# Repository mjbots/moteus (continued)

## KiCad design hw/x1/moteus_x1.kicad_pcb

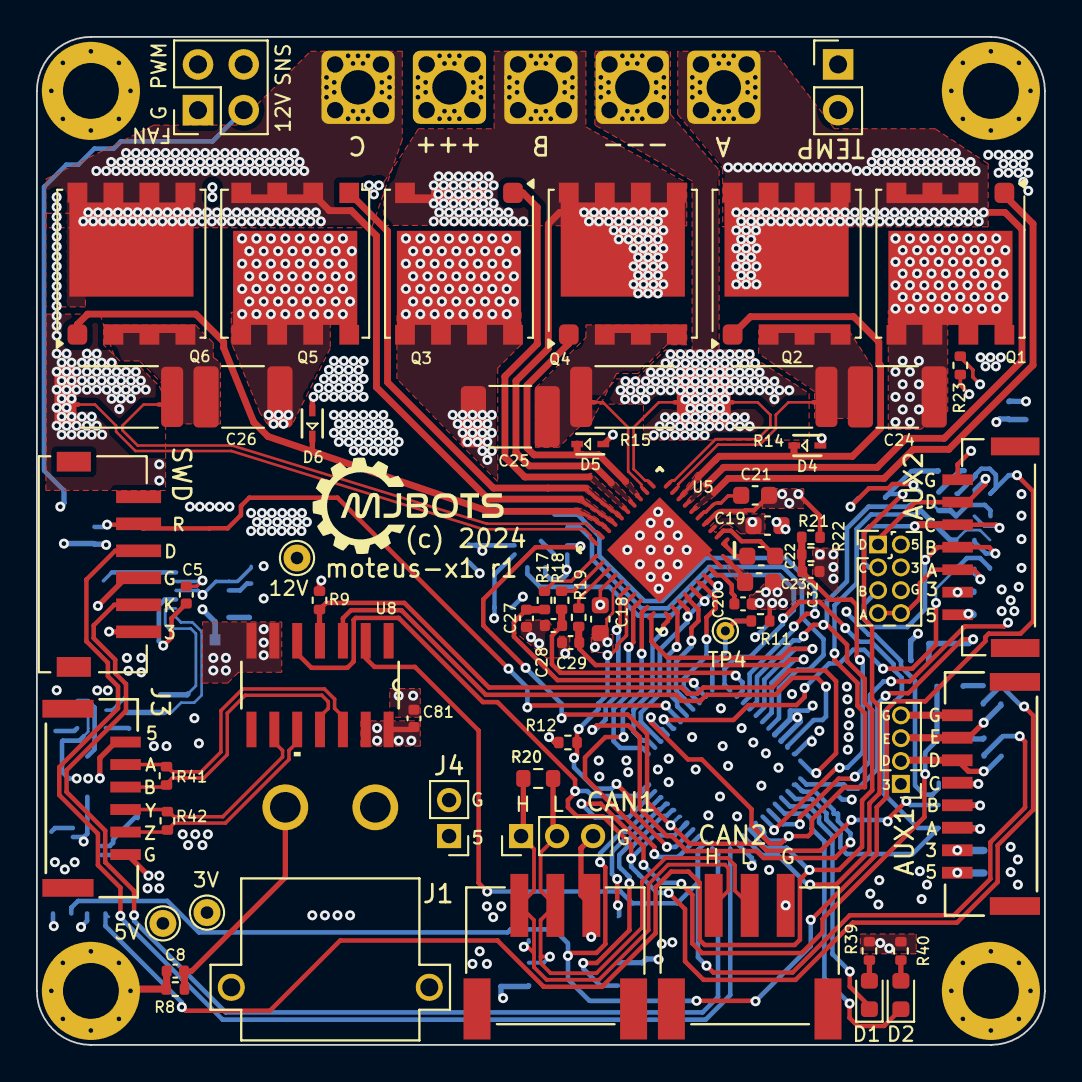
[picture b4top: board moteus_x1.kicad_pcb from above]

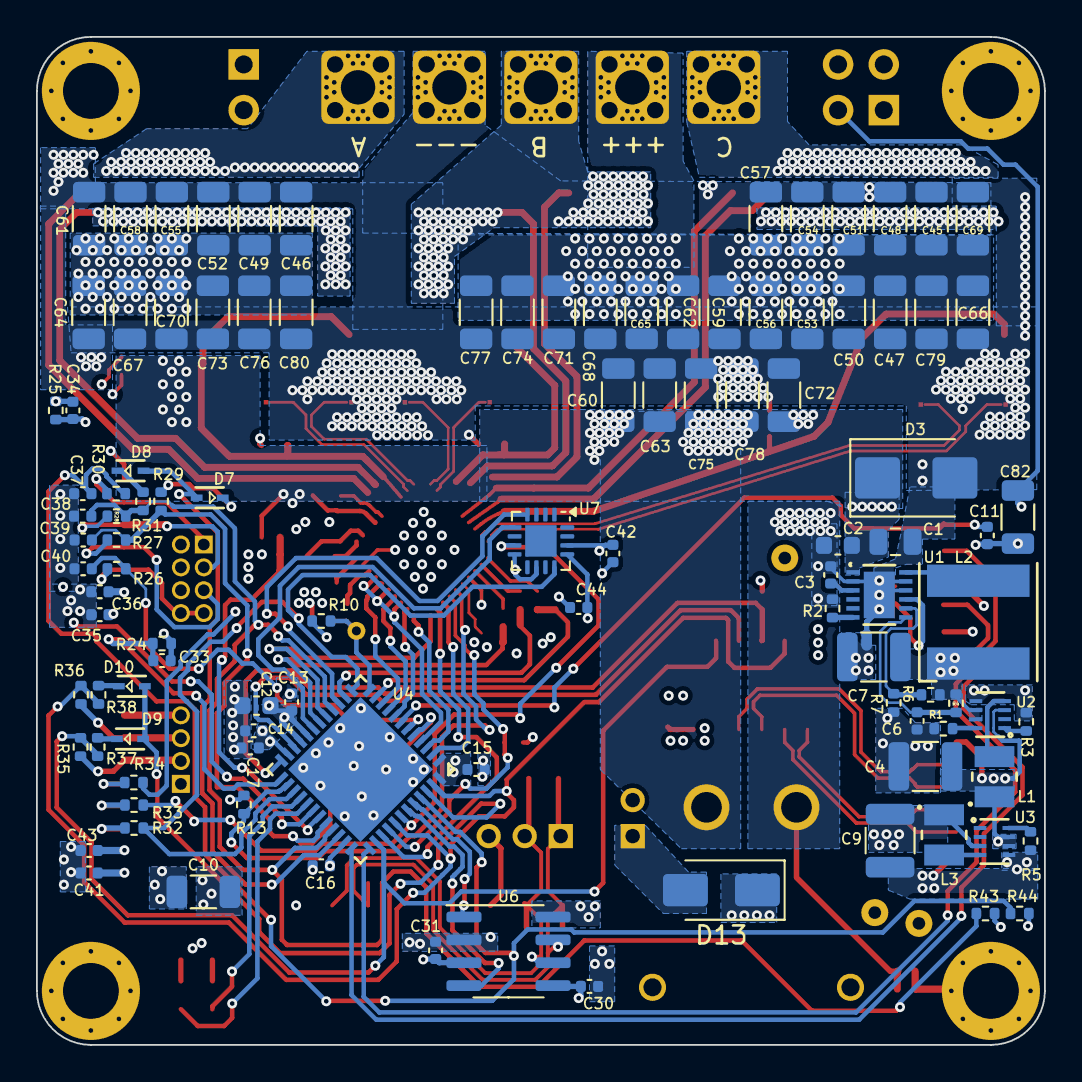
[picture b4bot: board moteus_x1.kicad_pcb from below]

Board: 6 copper layers, 56.0 x 56.0 mm, 187 parts (108 on the bottom side), 106 nets.

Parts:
AUX1: SM08B-GHS-TB; CONN_SM08B-GHS-TB_JST
AUX1_S1: Conn_01x04; PinHeader_1x04_P1.27mm_Vertical
AUX2: SM07B-GHS-TB(LF)(SN); JST_SM07B-GHS-TB(LF)(SN)
AUX2H1: Conn_02x04_Odd_Even; PinHeader_2x04_P1.27mm_Vertical
C1: 1uF 100V; C_0805_2012Metric
C2, C19: 0.1uF 100V; C_0603_1608Metric
C3, C6, C14, C20, C35, C36, C41, C42, C43: 1uF; C_0402_1005Metric
C4, C7, C9: 22uF; C_1210_3225Metric
C5: 5600pF; C_0402_1005Metric
C8, C37, C38, C39, C40: DNP; C_0402_1005Metric
C10: 10uF; C_1206_3216Metric
C11, C13, C15, C16, C17, C30, C31, C32, C33, C34, C44, C81: 0.1uF; C_0402_1005Metric
C12: 4.7uF; C_0603_1608Metric
C18, C23: 1uF; C_0603_1608Metric
C21: 1uF 25V; C_0603_1608Metric
C22: 47nF 100V; C_0603_1608Metric
C24, C25, C26: 0.1uF 100V; C_1812_4532Metric
C27, C28, C29: 1000pF; C_0402_1005Metric
C45, C46, C47, C48, C49, C50, C51, C52, C53, C54, C55, C56, C57, C58, C59, C60, C61, C62, C63, C64, C65, C66, C67, C68, C69, C70, C71, C72, C73, C74, C75, C76, C77, C78, C79, C80: 4.7uF 100V; C_1206_3216Metric
C82: 4.7uF; C_1206_3216Metric
CAN1, CAN2: S3B-PH-SM4-TB(LF)(SN); JST_S3B-PH-SM4-TB(LF)(SN)
CAN_DBG1: Conn_01x03_Pin; PinHeader_1x03_P2.00mm_Vertical
D1, D2: LED; LED_0603_1608Metric
D3: SMBJ51D-M3/I; D_SMB
D4, D5, D6, D7, D8, D9, D10: BAT41KFILM; SOD-523_STM
D13: US1B; D_SMA
FAN1: Conn_01x04_Pin; PinSocket_2x02_P2.54mm_Vertical
J1: XT30PW-M; AMASS_XT30PW-M
J3: SM06B-GHS-TB; CONN_SM06B-GHS-TB_JST
J4: Conn_01x02_Pin; PinHeader_1x02_P2.00mm_Vertical
L1, L3: 2.2uH; IND_DFE252012_MUR
L2: 100uH; IND_6028-WE-LQS_WRE
M1, M2, M3, M4: Conn_01x01_Pin; M3_MOUNT_CORNER
NT1: NetTie_2; NetTie-2_SMD_Pad0.254mm
NT2, NT3, NT4, NT5, NT6, NT7: NetTie_2; NetTie-2_SMD_Pad0.2
Q1, Q2, Q3, Q4, Q5, Q6: FDMT80080DC; PQFN_8x8
R1: 42.2k 1%; R_0402_1005Metric
R2: 69.8k 1%; R_0402_1005Metric
R3: 80.6k 1%; R_0402_1005Metric
R4, R17, R18, R19: 22; R_0402_1005Metric
R5: 52.3k 1%; R_0402_1005Metric
R6: 226k 1%; R_0402_1005Metric
R7: 16.2k 1%; R_0402_1005Metric
R8, R10: DNP; R_0402_1005Metric
R9, R12, R13, R29, R31, R37, R38: 2k; R_0402_1005Metric
R11, R21: 100k 1%; R_0402_1005Metric
R14, R15, R16: 0.5mOhm; R_2512_6332Metric
R20: 120; R_0603_1608Metric
R22: 4.7k 1%; R_0402_1005Metric
R23: 47k NTC; R_0402_1005Metric
R24, R25: 10k 1%; R_0402_1005Metric
R26, R27, R28, R30, R32, R33, R34, R35, R36, R43, R44: 100; R_0402_1005Metric
R39, R40: 560; R_0402_1005Metric
R41, R42: 120; R_0402_1005Metric
SWD1: S6B-ZR-SM4A-TF(LF)(SN); JST_S6B-ZR-SM4A-TF(LF)(SN)
TEMP1: Conn_01x02_Pin; PinHeader_1x02_P2.54mm_Vertical
TP1, TP2, TP3: TestPoint; TestPoint_THTPad_D1.5mm_Drill0.7mm
TP4: TestPoint; TestPoint_THTPad_D1.0mm_Drill0.5mm
U1: MAX17760ATC+; 21-0664E_1233-1C_MXM
U2, U3: TPS629203DRLR; SOT-5x3_DRL0008A_TEX
U4: STM32G474CEU6; UFQFPN-48_7X7X0P55MM
U5: DRV8353SRTAR; RTA0040B
U6: TCAN1057AEV-Q1; SOIC-8_3.9x4.9mm_P1.27mm
U7: MA600; QFN-16-1EP_3x3mm_P0.5mm_EP1.75x1.75mm
U8: SN65HVD35DR; D14
VN1: Conn_01x01; POWER_M2.5
VP1: Conn_01x01; POWER_M2.5
X1, X2, X3: Conn_01x01; POWER_M2.5

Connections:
+3V: AUX1.2, AUX1_S1.1, AUX2.2, AUX2H1.4, C9.1, C10.1, C12.1, C13.1, C14.1, C15.1, C16.1, C17.1, C18.2, C30.1, C36.1, C42.1, C43.1, C44.1, C81.1, L3.1, R10.1, R12.1, R13.1, R23.1, R39.1, R40.1, SWD1.6, TEMP1.1, TP3.1, U3.3 (VOS), U4.1 (VBAT), U4.20 (VREF+), U4.21 (VDDA), U4.23 (VDD), U4.35 (VDD), U4.48 (VDD), U5.24 (VREF), U6.5 (VIO), U7.13 (VDD), U7.14 (AVDD), U8.13 (VCC), U8.14 (VCC)
+5V: AUX1.1, AUX2.1, AUX2H1.2, C4.1, C31.1, C35.1, C41.1, D13.1 (K), J3.1, L1.1, TP1.1, U2.3 (VOS), U3.6 (VIN), U3.7 (EN), U6.3 (VCC)
+12V: C7.1, C19.2, C82.1, FAN1.2, L2.1, R4.2, R6.1, TP2.1, U2.6 (VIN), U2.7 (EN), U5.3 (VM)
/CAN/CAN_N: CAN1.2, CAN2.2, CAN_DBG1.2, R20.2, U6.6 (CANL)
/CAN/CAN_P: CAN1.1, CAN2.1, CAN_DBG1.1, R20.1, U6.7 (CANH)
/CAN/CAN_RX: U4.43 (PB5), U6.4 (RXD)
/CAN/CAN_TX: U4.44 (PB6), U6.1 (TXD)
/Current Sense/CUR1: R17.1, U5.21 (SOC)
/Current Sense/CUR2: R18.1, U5.22 (SOB)
/Current Sense/CUR3: R19.1, U5.23 (SOA)
/Current Sense/FCUR1: C27.1, R17.2, U4.11 (PA3)
/Current Sense/FCUR2: C28.1, R18.2, U4.14 (PA6)
/Current Sense/FCUR3: C29.1, R19.2, U4.18 (PB1)
/Gate Driver/CPH: C22.2, U5.2 (CPH)
/Gate Driver/CPL: C22.1, U5.1 (CPL)
/Gate Driver/DRV8323_CS: U4.17 (PB0), U5.30 (SCS_N)
/Gate Driver/DRV8323_FAULT: R13.2, U4.26 (PB13), U5.26 (FAULT_N)
/Gate Driver/DRV8323_MISO: R12.2, U4.40 (PC11), U5.27 (SDO)
/Gate Driver/DRV8323_MOSI: U4.2 (PC13), U5.28 (SDI)
/Gate Driver/DRV8323_SCLK: U4.39 (PC10), U5.29 (SCLK)
/Gate Driver/GHA: Q1.1 (G), U5.6 (GHA)
/Gate Driver/GHB: Q3.1 (G), U5.15 (GHB)
/Gate Driver/GHC: Q5.1 (G), U5.16 (GHC)
/Gate Driver/GLA: D4.1, Q2.1 (G), U5.8 (GLA)
/Gate Driver/GLB: D5.1, Q4.1 (G), U5.13 (GLB)
/Gate Driver/GLC: D6.1, Q6.1 (G), U5.18 (GLC)
/Gate Driver/MOTOR1: U4.8 (PA0), U5.32 (INHA)
/Gate Driver/MOTOR2: U4.9 (PA1), U5.34 (INHB)
/Gate Driver/MOTOR3: U4.10 (PA2), U5.36 (INHC)
/Gate Driver/MOTOR_ENABLE: U4.3 (PC14-OSC32_IN), U5.31 (ENABLE)
/Gate Driver/MOTOR_HIZ: U4.4 (PC15-OSC32_OUT), U5.33 (INLA), U5.35 (INLB), U5.37 (INLC)
/H Bridge A/OUTX: Q1.2 (S), Q2.3 (D), U5.7 (SHA), X1.1
/H Bridge A/SPX_Q: C24.2, NT2.2, Q2.2 (S), R14.1
/H Bridge A/SXX_N: NT3.1, U5.10 (SNA)
/H Bridge A/SXX_P: NT2.1, U5.9 (SPA)
/H Bridge B/OUTX: Q3.2 (S), Q4.3 (D), U5.14 (SHB), X2.1
/H Bridge B/SPX_Q: C25.2, NT4.2, Q4.2 (S), R15.1
/H Bridge B/SXX_N: NT5.1, U5.11 (SNB)
/H Bridge B/SXX_P: NT4.1, U5.12 (SPB)
/H Bridge C/OUTX: Q5.2 (S), Q6.3 (D), U5.17 (SHC), X3.1
/H Bridge C/SPX_Q: C26.2, NT6.2, Q6.2 (S), R16.1
/H Bridge C/SXX_N: NT7.1, U5.20 (SNC)
/H Bridge C/SXX_P: NT6.1, U5.19 (SPC)
/LED Sense/DAC: R10.2, R11.1, TP4.1, U4.12 (PA4)
/LED Sense/LED1: D1.1 (K), U4.28 (PB15)
/LED Sense/LED2: D2.1 (K), U4.29 (PC6)
/Power Input/5V_IN: D13.2 (A), J4.1
/VT Sense/VBAT_SENSE: C32.1, R21.2, R22.1, U4.31 (PA9)
/VT Sense/VTEMP_FET: C33.1, R23.2, R24.1, U4.25 (PB12)
/VT Sense/VTEMP_MOT: C34.1, R25.1, TEMP1.2, U4.30 (PA8)
/aux1/AS5047_CS: U4.19 (PB2), U7.5 (~CS)
/aux1/AUX1P_A: AUX1.3, R32.1
/aux1/AUX1P_B: AUX1.4, R33.1
/aux1/AUX1P_C: AUX1.5, R34.1
/aux1/AUX1P_D: AUX1.6, AUX1_S1.2, R35.1
/aux1/AUX1P_E: AUX1.7, AUX1_S1.3, R36.1
/aux1/AUX1_A: R32.2, U4.13 (PA5), U4.27 (PB14), U7.12 (SCLK)
/aux1/AUX1_B: R33.2, U4.42 (PB4), U7.7 (MISO)
/aux1/AUX1_C: R34.2, U4.15 (PA7), U7.4 (MOSI)
/aux1/AUX1_D: R35.2, R37.2, U4.38 (PA15), U8.2 (R)
/aux1/AUX1_E: R36.2, R38.2, U4.41 (PB3), U4.47 (PB9), U8.5 (D)
/aux1/AUX1_I2C_PULLUP: D9.2, D10.2, U4.46 (PB8-BOOT0)
/aux2/AUX2P_A: AUX2.3, AUX2H1.7, AUX2H1.8, R26.1
/aux2/AUX2P_B: AUX2.4, AUX2H1.5, R27.1
/aux2/AUX2P_C: AUX2.5, AUX2H1.3, R28.1
/aux2/AUX2P_D: AUX2.6, AUX2H1.1, R30.1
/aux2/AUX2_A: C40.1, R26.2, U4.6 (PF1-OSC_OUT)
/aux2/AUX2_B: C39.1, R27.2, R29.2, U4.5 (PF0-OSC_IN), U4.32 (PA10)
/aux2/AUX2_C: C38.1, R28.2, R31.2, R43.1, U4.16 (PC4), U4.33 (PA11)
/aux2/AUX2_D: C37.1, R30.2, R44.1, U4.45 (PB7)
/aux2/AUX2_I2C_PULLUP: D7.2, D8.2, U4.34 (PA12)
/rs422/RS422_DE: R9.1, U4.24 (PB11), U8.4 (DE)
/rs422/RS422_RE: U4.22 (PB10), U8.3 (*RE)
/rs422/RS422_RX_N: J3.3, R41.2, U8.11 (B)
/rs422/RS422_RX_P: J3.2, R41.1, U8.12 (A)
/rs422/RS422_TX_N: J3.5, R42.2, U8.10 (Z)
/rs422/RS422_TX_P: J3.4, R42.1, U8.9 (Y)
/stm32g4/NRST: C11.1, SWD1.2, U4.7 (PG10-NRST)
/stm32g4/SWCLK: SWD1.5, U4.37 (PA14)
/stm32g4/SWDIO: SWD1.3, U4.36 (PA13)
GND: AUX1.8, AUX1_S1.4, AUX2.7, AUX2H1.6, C4.2, C6.2, C7.2, C9.2, C10.2, C11.2, C12.2, C13.2, C14.2, C15.2, C16.2, C17.2, C18.1, C20.1, C23.1, C27.2, C28.2, C29.2, C30.2, C31.2, C32.2, C33.2, C34.2, C35.2, C36.2, C37.2, C38.2, C39.2, C40.2, C41.2, C42.2, C43.2, C44.2, C81.2, C82.2, CAN1.3, CAN2.3, CAN_DBG1.3, FAN1.1, J3.6, J4.2, NT1.2, R1.2, R3.2, R5.2, R7.2, R9.2, R11.2, R22.2, R24.2, R25.2, SWD1.4, U2.5 (GND), U3.5 (GND), U4.49 (EPAD), U5.25 (AGND), U6.2 (GND), U6.8 (STB), U7.8 (GND), U7.10 (TEST), U8.6 (GND), U8.7 (GND)
GNDPWR: C1.2, C2.2, C3.2, C5.2, C8.2, C19.1, C45.2, C46.2, C47.2, C48.2, C49.2, C50.2, C51.2, C52.2, C53.2, C54.2, C55.2, C56.2, C57.2, C58.2, C59.2, C60.2, C61.2, C62.2, C63.2, C64.2, C65.2, C66.2, C67.2, C68.2, C69.2, C70.2, C71.2, C72.2, C73.2, C74.2, C75.2, C76.2, C77.2, C78.2, C79.2, C80.2, D3.2 (A2), D4.2, D5.2, D6.2, J1.N, NT1.1, NT3.2, NT5.2, NT7.2, R2.2, R8.2, R14.2, R15.2, R16.2, U1.2 (PGND), U1.10 (MODE), U1.11 (SGND), U1.13 (EPAD), U5.39 (PGND), U5.41 (PAD), VN1.1
MOUNT_GND: C8.1, M4.1, R8.1
unnamed: D1.2 (A), R39.2
unnamed: D2.2 (A), R40.2
unnamed: D7.1, R29.1
unnamed: D8.1, R31.1
unnamed: D9.1, R37.1
unnamed: D10.1, R38.1
unnamed: FAN1.3, R44.2
unnamed: FAN1.4, R43.2
unnamed: C6.1, R4.1, U1.7 (EXTVCC)
unnamed: R6.2, R7.1, U1.8 (FB)
unnamed: L2.2, U1.12 (LX)
unnamed: R2.1, U1.6 (RT/SYNC)
unnamed: C5.1, U1.9 (SS)
unnamed: C3.1, U1.3 (VCC)
unnamed: R3.1, U2.1 (FB/VSET)
unnamed: R1.1, U2.8 (MODE/S-CONF)
unnamed: L1.2, U2.4 (SW)
unnamed: R5.1, U3.8 (MODE/S-CONF)
unnamed: L3.2, U3.4 (SW)
unnamed: C20.2, U5.38 (DVDD)
unnamed: C21.2, U5.5 (VCP)
unnamed: C23.2, U5.40 (VGLS)
V+: C1.1, C2.1, C21.1, C24.1, C25.1, C26.1, C45.1, C46.1, C47.1, C48.1, C49.1, C50.1, C51.1, C52.1, C53.1, C54.1, C55.1, C56.1, C57.1, C58.1, C59.1, C60.1, C61.1, C62.1, C63.1, C64.1, C65.1, C66.1, C67.1, C68.1, C69.1, C70.1, C71.1, C72.1, C73.1, C74.1, C75.1, C76.1, C77.1, C78.1, C79.1, C80.1, D3.1 (A1), J1.P, Q1.3 (D), Q3.3 (D), Q5.3 (D), R21.1, U1.1 (VIN), U5.4 (VDRAIN), VP1.1

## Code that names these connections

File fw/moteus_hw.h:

// Copyright 2023 mjbots Robotic Systems, LLC.  info@mjbots.com
//
// Licensed under the Apache License, Version 2.0 (the "License");
// you may not use this file except in compliance with the License.
// You may obtain a copy of the License at
//
//     http://www.apache.org/licenses/LICENSE-2.0
//
// Unless required by applicable law or agreed to in writing, software
// distributed under the License is distributed on an "AS IS" BASIS,
// WITHOUT WARRANTIES OR CONDITIONS OF ANY KIND, either express or implied.
// See the License for the specific language governing permissions and
// limitations under the License.

#pragma once

#include "mbed.h"

#include "fw/fet_thermal_model.h"
#include "fw/millisecond_timer.h"

namespace moteus {

//////////////////////////////////////////
// The following "families" are supported:
//  moteus-r4 - family 0
//  moteus-n1 - family 1
//  moteus-c1 - family 2
//  moteus-x1 - family 3
//  moteus-r5 - family 4
//
// Each family has an independent hardware version timeline, and
// possibly a different mechanism for verifying hardware version
// compatibility.


// This structure is filled in once the family and hardware version
// are known.
struct MoteusHwPins {
  PinName pwm1 = PA_0_ALT0;
  PinName pwm2 = PA_1_ALT0;
  PinName pwm3 = PA_2_ALT0;

  PinName drv8323_enable = NC;
  PinName drv8323_hiz = NC;
  PinName drv8323_cs = NC;

  PinName drv8323_mosi = NC;
  PinName drv8323_miso = NC;
  PinName drv8323_sck = NC;
  PinName drv8323_fault = NC;

  PinName debug_led1 = NC;
  PinName power_led = NC;

  PinName current1 = NC;
  PinName current2 = NC;
  PinName current3 = NC;

  PinName vsense = NC;
  PinName tsense = PA_9;

  PinName msense = NC;

  float vsense_adc_scale = 0.0f;

  PinName as5047_cs = NC;

  PinName can_td = NC;
  PinName can_rd = NC;

  PinName debug1 = NC;
  PinName debug2 = NC;
  PinName debug_dac = PA_4;

  uint32_t model_number = 0;

  uint32_t firmware_version = 0x000105;

  // Each board has a power limit curve, below a bus voltage V_l, the
  // P_l power limit is used.  Above bus voltage V_h, P_h power limit
  // is used.  Between, the power limit is linearly interpolated.  All
  // power limits are normalized to 30kHz PWM.
  float power_P_l_W = 0.0f;
  float power_V_l = 24.0f;
  float power_P_h_W = 0.0f;
  float power_V_h = 34.0f;

  // Constants for the FET junction temperature estimator.  Every
  // board must provide these.  See fw/fet_thermal_model.h.
  FetThermalParams fet_thermal;
};


struct FamilyAndVersion {
  int family = 0;
  int hw_version = 0;
  int hw_pins = 0;
};

// Return what family we are executing on.
FamilyAndVersion DetectMoteusFamily(MillisecondTimer*);

MoteusHwPins FindHardwarePins(FamilyAndVersion);


// The "FIRMWARE_VERSION" is a misnomer.  It instead is the equivalent
// of an ABI version, and is incremented when configuration values
// change in a way that would not result in equivalent behavior across
// an upgrade/downgrade.

// Version history:

// # 0x0101 #
//
// * Fixed the calculation of feedforward voltage to have the correct
//   sign for the velocity component.  Previous firmwares,
//   inappropriately applied a negative feedforward term, which
//   counteracted rotation instead of being an actual feedforward.

// # 0x0102 #
//
// * Removed servo.feedforward_scale entirely

// # 0x0103 #
//
// * Added servo.pwm_scale, and for r4.8 boards changed the default
//   value of pwm_comp_off / pwm_comp_mag.

// # 0x0104 #
//
// * Added configurable PWM rates, which changed default values of
//   pwm_comp_mag and pwm_comp_off.

// # 0x0105 #
//
// * Switched to a new encoder and position subsystem.

// # 0x0106 #
//
// * Switched aux?.sources.x.i2c.poll_ms to poll_rate_us to match UART
//   and give more resolution.

// # 0x0107 #
//
// * Fixed motor_position.output.sign == -1 so that DQ commands for
//   voltage or current are inverted, so that positive Q axis voltage
//   or current results in positive speed

// # 0x0108 #
//
// * The default value of `servo.bemf_feedforward` was changed from
//   1.0 to 0.0.

// # 0x0109 #
//
// * Commutation compensation now interpolates, which means old tables
//   need to be upgraded during the flash process.
// * The motor thermistor value is now configurable and defaults to
//   10k instead of 47k.

// # 0x010a #
//
// * servo.max_power_W now defaults to NaN, and if present is used as
//   an absolute value rather than as a "nominal" value.

// # 0x010b #
//
// * servo.flux_brake_margin_voltage replaces
//   servo.flux_brake_min_voltage
// * servo.temperature_margin replaces servo.derate_temperature
// * servo.motor_temperature_margin replaces
//   servo.motor_derate_temperature

// # 0x010c #
//
// * motor_position.sources.x.pll_filter_hz was previously specified
//   in terms of a somewhat arbitrary "natural frequency", but is now
//   specified in terms of the 3dB cutoff frequency

// # 0x010d #
//
// * aux?.rs422 replaced aux?.uart.rs422 as now the RS422 transceiver
//   can be enabled for both UART and BiSS-C encoders

// # 0x010e #
//
// * servo.pid_dq.kp/ki/max_desired_rate replaced by servo.pid_dq_hz
//   and servo.max_current_desired_rate.  PI gains are now computed
//   automatically from the bandwidth and motor parameters.

// # 0x010000
//
// No functional changes.  ABI release 1.0.0

// # 0x010100
//
// * The drv8323_conf reg4 calculation now maps idriven_ls_ma through the
//   DRV8353 pull-down (idriven) table instead of the pull-up (idrivep)
//   table.  DRV8353-board idriven_ls_ma defaults were adjusted and
//   moteus_tool migrates stored configs so the gate-drive register
//   output is unchanged across the upgrade.
// * The gate-driver family routing was corrected: moteus-c1 (family 2,
//   a DRV8323) now uses the drv8323 register path and moteus-n1
//   (family 1, a DRV8353) uses the drv8353 register path.  These were
//   swapped by an inadvertent "family == 1" clause in the c1-support
//   commit.  c1's defaults are adjusted (and configs migrated) to keep
//   its register output unchanged; n1's register output is restored to
//   what it was before the c1-support commit.
//
// ABI release 1.1.0

#define MOTEUS_MODEL_NUMBER 0x0000
#define MOTEUS_FIRMWARE_VERSION 0x010100

extern MoteusHwPins g_hw_pins;

// Ensure the DRV8323 is turned off.
void MoteusEnsureOff();

}

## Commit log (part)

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2026-05-15 Add jerk-limited online trajectory generation
    When data->jerk_limit is finite and positive, the position trajectory
    generator slews control_acceleration at no more than the configured
    rate per second, producing an S-curve velocity profile instead of a
    bang-bang trapezoidal one. The behavior reduces to the legacy path
    when jerk_limit is NaN, so out-of-the-box trajectories are unchanged.
    This is not a complete substitute for systems like ruckig, notably:
2026-05-15 Tighten bounds across jerk-related tests
    Replace generous safety factors with empirically-derived tight
    bounds. Tightening summary:
    - ResidualBound: 10x -> 1x safety factor over the analytical
    (kinematic_floor + drift_floor). Worst observed across all jerk
    tests is ~30% of the unscaled bound, so 1x retains >3x headroom.
    - JerkBoundFor + the duplicate in RunAndCheckJerkBound + the in-line
2026-05-15 Verify jerk-bound per cycle in JerkLimitedTakesLongerThanTrapezoidal
    The comment claimed the jerk-limited run should have no |Δa| > j*dt
    per cycle, but no such assertion existed. Add it: the run lambda
    now captures control_acceleration each cycle and (for the
    jerk-limited variant only) asserts |Δa| <= j*dt + accel*eps.
    Verified by replacing SlewAcceleration's per-cycle clamp with 2x the
    bound; the new check fires immediately (1.33 > 0.667).
2026-05-15 Test consolidation pass 2: subsume parameterizable singletons
    Three more groups subsumed into existing or new sweeps. Each
    consolidation was verified by reverting the relevant fix and
    confirming the consolidated test still catches the regression.
    Section E (mid-slew retargeting):
    - Extend JerkLimitRetargetAtEachPhase to accept `new_target`
    per row (was hard-coded 10.0) and to recognise `delay < 0`
2026-05-15 Stop NaN'ing data->position at jerk-limited termination
    The previous fix (c394983a) made the trajectory_done reset
    conditional on the commit latch -- but only protected the cycle
    the host frame actually arrived on. In production the host polls
    every ~2 ms, leaving ~60 ISR cycles between frames during which the
    FW used to NaN'd data->position out of the just-completed
    trajectory. The latch tolerance check (data->position == cp) then
2026-05-16 Add termination sweeps for four previously-uncovered scenarios
    Four new tests covering scenarios that production failures suggest
    the original tests do not exercise:
    - JerkLimitMoveLoopTermination: the moteus.move_to() loop pattern
    (a sequence of four same/different targets across two channels,
    three iterations). Catches any failure where consecutive moves
    to the same target oscillate or fail to terminate -- the exact
2026-05-16 Add hall lost-tracking recovery for stuck misaligned motors
    When hall sensors are physically misaligned (sector widths not
    uniformly 60° electrical), the firmware's filtered_value can coast
    forward to compensated + max_err during the wider sectors and then
    stay there once the motor stops -- with no transition to "reset"
    commutation, the firmware-reported electrical angle can sit nearly
    90° from the rotor's true angle, the projected q-axis torque
2026-05-19 Deployed 39e1a6a with MkDocs version: 1.6.1
2026-05-19 Do a better job estimating the ground truth hall position
    The find_ground_truth function used to return the start of a sector
    and velocity=0 when either the trace ended or when the rotor bounced
    back and forth.
    Instead, for end of trace return the center of the sector, and if the
    rotor bounced back and forth, return the boundary itself, as we have
    no real indication that it went into the sector at all.
2026-05-21 Deployed ad43136 with MkDocs version: 1.6.1
2026-05-21 Actually update CHANGELOG.md since the last release
2026-05-22 Deployed e1333e5 with MkDocs version: 1.6.1
2026-05-23 Fix more doc config typos
2026-05-23 Rewrite mypy_test to operate on the build files
    Previously it generated a fake version file in the actual source tree
    which was often left behind.
2026-05-24 Deployed eb7c5fc with MkDocs version: 1.6.1
2026-05-24 Deployed e4459e7 with MkDocs version: 1.6.1
2026-05-24 Release python 1.0.0rc2
2026-05-25 Release python 1.0.0rc3
2026-05-25 Release python 1.0.0rc4
2026-05-27 Fix multiple gate drive strength mapping issues and re-tune the n1
    There were two separate bugs in involved here.
    1. For drv8353 boards, we were accidentally using the gate mapping
    table for idrivep on the low side when we should have been using
    idriven.
    2. We were mis-characterizing moteus-c1 as a drv8353 board and have
    been mis-characterizing moteus-n1 as a drv8323 board since the
2026-05-28 Release python 1.0.0
2026-06-03 Fix the location of the default UART port
    The intention was that the default UART port would always be present
    on pins that were connectorized. That is what is documented.
    However, the actual implementation of this was broken, and moteus-c1
    got its default UART on aux1, whereas moteus-n1 got it on aux2. Swap
    those back to what was intended.
    Now, the default UARTs are at:
2026-06-03 Deployed ae2d7a77 with MkDocs version: 1.6.1
2026-06-03 Rust API: Fix MSRV to 1.75 (was incorrectly set to 1.85)
2026-06-03 Rust API: Fix version numbers in docs/integration/rust.md
2026-06-03 Rust API: Add Transport::from_device() for single-device construction
2026-06-03 Rust API: Use fixed-size arrays instead of Vec for single-request cycles
2026-06-03 Rust API: Add AsyncController
    - AsyncController: High-level async interface using tokio feature
    - Full module exports in lib.rs
2026-06-03 Rust API: Rename Request builder methods with with_ prefix
2026-06-03 Rust API: Add SocketCAN transport for Linux
    Add SocketCAN transport for native Linux CAN interfaces:
    - SocketCan: Linux kernel CAN interface support
    - CAN-FD frame send/receive
    - Interface enumeration
2026-06-03 Rust API: Fix all cargo clippy warnings
    Applied automatic fixes and manual corrections for: unnecessary casts
    left over from f64->f32 migration, doc comment overindentation,
    map_or -> is_none_or/is_some_and, derivable Default impl for
    FrameFilter, while_let_loop, iter().copied().collect() -> to_vec(),
    and suppressed needless_range_loop where refactoring would reduce
    readability.
2026-06-03 Rust API: Add #[non_exhaustive] to all public structs and enums
    Prevents future field or variant additions from being breaking changes
    for external crate users. Internal code is unaffected.
2026-06-03 Rust API: Fix moteus-protocol feature documentation
2026-06-03 Rust API: Revert edition to 2021 to preserve MSRV 1.75
2026-06-03 Rust API: Simplify Explicit Transport doc example
2026-06-03 Rust API: Fix SocketCanFactory references for cross-platform builds
    Cfg-gate get_factories(), get_async_factories(), and related tests
    that reference SocketCanFactory/AsyncSocketCanFactory so they only
    compile on Linux. This fixes builds on non-Linux platforms.
2026-06-03 Rust API: Add doc tests to bazel test suite, convert ignore to no_run
    Add rust_doc_test targets for both base and all-features variants.
    Convert all `ignore` doctests to `no_run` (compiled but not executed)
    where possible, and fix doc examples to compile correctly. Only 3
    examples remain `ignore` in the base target (require tokio/clap
    features) but are tested by the all-features variant.
2026-06-03 Rust API: Trim root re-exports to core types only
    Reduce the moteus crate root from ~46 re-exports to ~12 core types
    that most users need. Advanced types remain accessible through their
    public modules (e.g., moteus::diagnostic::DiagnosticStream,
    moteus::transport::transaction::Request). This makes auto-complete
    more useful and the API surface easier to understand.
2026-06-03 Rust API: Remove SocketCan stubs on non-Linux, cfg-gate factory impls
    SocketCan is only available on Linux. Rather than providing stub types
    that fail at runtime, cfg-gate the struct, factory impl, and registry
    entry so they simply don't exist on non-Linux platforms.
2026-06-03 Rust API: Add #[must_use] to derived setter methods
2026-06-03 Rust API: Make multiplex module pub(crate), keep scaling public
    The multiplex module's types are re-exported at the crate root; the
    raw protocol command byte constants are also re-exported for users who
    need them. The scaling module stays public since users interact with
    scaling consts directly via Value::to_f32().
2026-06-03 rust: Rename transport structures to match python more closely
    - the structures that directly communicate with a device now get a
    'Device' suffix like in python
    - the TransportOps trait is now Transport
    - the Transport struct is now Router
    Then, there are new wrappers named 'Fdcanusb' and 'SocketCan' which
    are a 'Router' that is composed of a single device of the given type.
2026-06-03 Rust API: Add transport registry for external factory registration
    External crates can now register transport factories via register() and
    register_async() so they participate in auto-detection. Adds extra field
    to TransportOptions for transport-specific key-value args, moves
    factory-specific arg specs into arg_specs() trait methods, and replaces
    static TRANSPORT_ARG_SPECS with dynamic transport_arg_specs().
2026-06-03 rust: Add separate READMEs for each crate
2026-06-03 Reset I2C peripherals that appear to be taking too long
    If the STM32 I2C peripheral attempts to start a transaction with when
    both lines read low, it will itself hold both lines low, wedging with
    no way to get unstuck. Thus we use a brute-force timeout to reset the
    peripheral if a response doesn't come in on time.
2026-06-03 Deployed 46ca6586 with MkDocs version: 1.6.1
2026-06-10 Bump bytes from 1.11.0 to 1.11.1 in /lib/rust
    Bumps [bytes](https://github.com/tokio-rs/bytes) from 1.11.0 to 1.11.1.
    - [Release notes](https://github.com/tokio-rs/bytes/releases)
    - [Changelog](https://github.com/tokio-rs/bytes/blob/master/CHANGELOG.md)
    - [Commits](https://github.com/tokio-rs/bytes/compare/v1.11.0...v1.11.1)
    ---
    updated-dependencies:
2026-06-10 Deployed 0b3c7768 with MkDocs version: 1.6.1
2026-06-10 Deployed a30c3116 with MkDocs version: 1.6.1
2026-06-10 rust: Normalize capitalization of fdcanusb
2026-06-13 Deployed 3f62e5ed with MkDocs version: 1.6.1
2026-06-17 rust: Improvements to support out-of-crate transports
    Specifically, these changes are in service of eventual pi3hat support,
    which needs to have parent transports with no ability to communicate
    at all, but that merely contain children.
    Also, provide a mechanism for ArgSpec to be created from outside the
    crate.
2026-06-17 Deployed c84da142 with MkDocs version: 1.6.1
2026-06-17 Do a better job reporting how much space the disk cleanup saves
2026-06-17 Remove some stale documentation text about velocity mode
    There is a full example just below which is not stale, so there is no
    real reason to have this here anymore.
2026-06-17 Deployed 421fd6e6 with MkDocs version: 1.6.1
2026-06-17 Clarify that we are using bazel platforms
2026-06-17 Deployed e75764d0 with MkDocs version: 1.6.1
2026-06-18 debug: emit control_velocity in high-rate debug (bit 28)
2026-06-18 Deployed 7b4e6c9c with MkDocs version: 1.6.1
2026-06-25 First draft of mjuart
    This is just a simple FT231XQ breakout board with a ZH4 connector to
    be used as a high rate UART adapter with moteus controllers. It can
    receive data from the high rate debug port at 3Mbps or be used at
    1Mbps to command and monitor.
2026-06-25 mjuart: Define soldermask colors
